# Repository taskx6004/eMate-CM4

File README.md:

# eMate-CM4
Yet another CM4 form-factor design for eMate laptop conversion kit.

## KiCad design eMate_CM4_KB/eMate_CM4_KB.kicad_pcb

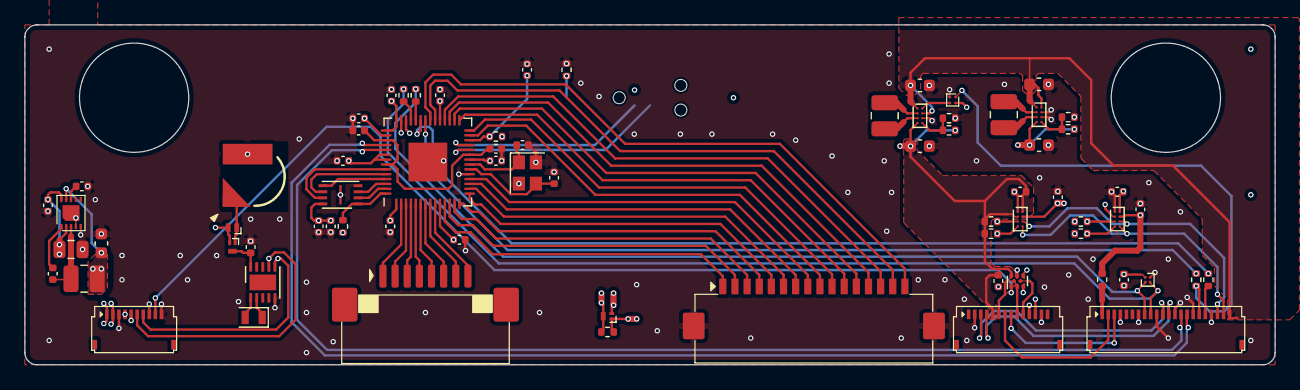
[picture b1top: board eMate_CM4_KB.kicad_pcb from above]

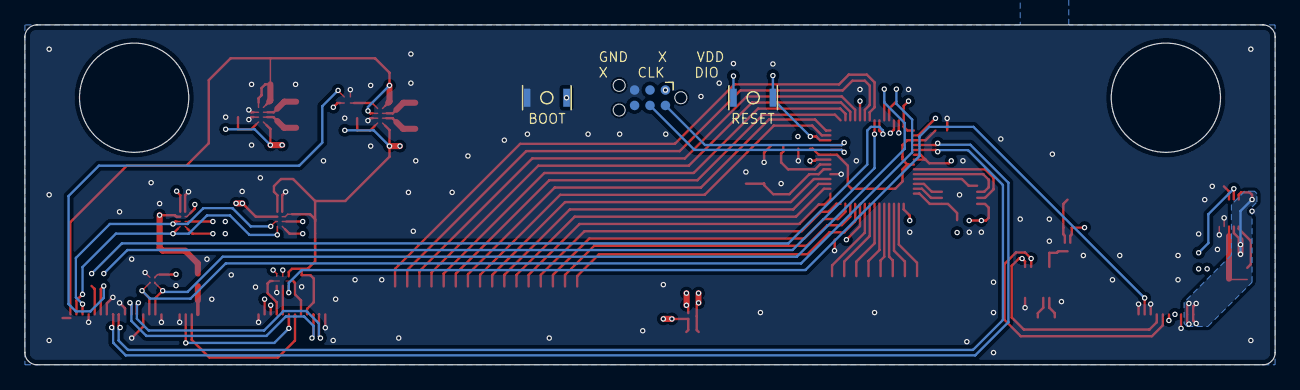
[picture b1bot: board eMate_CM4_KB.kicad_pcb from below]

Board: 4 copper layers, 103.0 x 28.0 mm, 75 parts (3 on the bottom side), 85 nets.

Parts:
BT1: XH414HG-IV01E
C1, C4, C6, C9, C13, C15, C17, C18, C19, C20, C21, C22, C23, C24, C27, C28, C29, C30: 100nF; C_0402_1005Metric
C2, C7, C10: 22uF; C_0603_1608Metric
C3, C11: 47uF; C_0603_1608Metric
C5: 4.7uF; C_0805_2012Metric
C8: 1uF; C_0402_1005Metric
C12, C14, C16: 2.2uF; C_0402_1005Metric
C25, C26: 15pF; C_0402_1005Metric
D1, D3: BAT54CM,315; Diodes_DFN1006-3
D2: BAS70L,315; Diodes_DFN1006-2
J1: FH34SRJ-22S-0.5SH(50)
J2: FH34SRJ-14S-0.5SH(50)
J3: FH34SRJ-10S-0.5SH(50)
J4: 522070833
J5: FH12-16S-1SH(55)
J6: TC2030-NL
L1, L3: 1uH; L_1008_2520Metric
L2: 10uH; L_1008_2520Metric
R1, R4, R6: 511k; R_0402_1005Metric
R2, R5: 91k; R_0402_1005Metric
R3, R17: 0; R_0402_1005Metric
R7, R8, R9, R10, R11, R12: 1k; R_0402_1005Metric
R13, R14, R15, R16: 4.7k; R_0402_1005Metric
SW1, SW2: EVPAWBD4A; EVPAWBA2A
U1: PCF85063ATL; DFN-10-1EP_2.6x2.6mm_P0.5mm_EP1.3x2.2mm
U2, U6: TPS631010YBGR; Texas_DSBGA-8_0.705x1.468mm_Layout2x4_P0.4mm
U3: SN74LVC1G06YZVR
U4: MAX77596ETBB+; MAX77596ETBB+T
U5: TCA9536ADTMR
U7: CAT24C32C5CTR; WLP-4_0.83x0.83mm_P0.4mm
U8: W25Q16JVUXIQ
U9: RP2040; QFN-56-1EP_7x7mm_P0.4mm_EP3.2x3.2mm
U10, U11: PCA9306YZTR; Texas_DSBGA-8_0.705x1.468mm_Layout2x4_P0.4mm
Y1: FC-12M32.768KHZ7PF20PPM; Crystal_SMD_2012-2Pin_2.0x1.2mm
Y2: 12MHz; Crystal_SMD_2520-4Pin_2.5x2.0mm

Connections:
3V3: C28.2, C30.2, R17.2, U10.B2 (VREF2), U11.B2 (VREF2)
3V3_BB1: C3.1, C9.2, C27.2, J2.5, J3.4, J3.5, R1.1, R13.2, R14.2, U2.D1 (VOUT), U5.7 (Vcc), U10.A2 (EN), U10.B1 (VREF1)
3V3_BB2: C12.2, C13.2, C16.2, C17.2, C18.2, C19.2, C20.2, C21.2, C22.2, C23.2, C29.2, D1.2, D2.2 (A), D3.3, J6.1 (VCC), R3.2, R6.1, R15.2, R16.2, U3.A2 (VDD), U7.A1 (VCC), U8.8 (VCC), U9.1 (IOVDD), U9.10 (IOVDD), U9.22 (IOVDD), U9.33 (IOVDD), U9.42 (IOVDD), U9.43 (ADC_AVDD), U9.44 (VREG_IN), U9.48 (USB_VDD), U9.49 (IOVDD), U11.A2 (EN), U11.B1 (VREF1)
/5V_~EN: J1.18, R10.2
/AD.DMICCLK: J1.2, J2.7
/AD.DMICIN: J1.3, J2.8
/CM4_I^{2}C_0.SCL: J1.20, U10.C2 (SCL2), U11.C2 (SCL2)
/CM4_I^{2}C_0.SDA: J1.21, U10.D2 (SDA2), U11.D2 (SDA2)
/CM4_I^{2}C_ID.SCL: J1.8, R11.2, U7.B1 (SCL)
/CM4_I^{2}C_ID.SDA: J1.9, R12.2, U7.B2 (SDA)
/EXT.D+: J1.11, J2.3
/EXT.D-: J1.12, J2.4
/FCM.ALS_SCL: J2.11, R13.1, U10.C1 (SCL1)
/FCM.ALS_SDA: J2.12, R14.1, U10.D1 (SDA1)
/FCM.ASL_INT: J2.10, U5.4 (P3/~INT)
/FCM.CAM_SW: J2.6, U5.8 (P1)
/FCM.MIC_SW: J2.9, U5.2
/HUB.D2+: J1.14, U9.47 (USB_DP)
/HUB.D2-: J1.15, U9.46 (USB_DM)
/I2C_GPIO.P0: J3.9, U5.1 (P0)
/M2.EN: J1.17, R9.2, U3.A1 (A)
/SCL: J3.6, R15.1, U1.7 (SCL), U5.5 (SCL), U9.41 (GPIO29_ADC3), U11.C1 (SCL1)
/SDA: J3.7, R16.1, U1.6 (SDA), U5.6 (SDA), U9.40 (GPIO28_ADC2), U11.D1 (SDA1)
GND: BT1.2 (-), C1.1, C2.2, C3.2, C5.2, C6.2, C7.2, C8.2, C9.1, C10.2, C11.2, C12.1, C13.1, C14.1, C15.1, C16.1, C17.1, C18.1, C19.1, C20.1, C21.1, C22.1, C23.1, C24.1, C25.1, C26.1, C27.1, C28.1, C29.1, C30.1, J1.4, J1.7, J1.10, J1.13, J1.16, J1.19, J2.2, J2.13, J3.3, J3.8, J3.10, J5.MP (MountPin), J6.5 (GND), R2.2, R5.2, R7.2, SW2.2, U1.5 (VSS), U2.C2 (GND), U3.B1 (GND), U4.4 (PGND), U4.5 (AGND), U4.EP (GND), U5.3 (GND), U6.B2 (MODE), U6.C2 (GND), U7.A2 (VSS), U8.4 (GND), U8.9 (EP), U9.19 (TESTEN), U9.57 (GND), U10.A1 (GND), U11.A1 (GND), Y2.2, Y2.4
HVSYS: C5.1, C6.1, J3.1, J3.2, U4.2 (SUP), U4.10 (EN)
unnamed: BT1.1 (+), D1.1, D2.1 (K)
unnamed: J1.1, R17.1
unnamed: J4.1, U9.2 (GPIO0)
unnamed: J4.2, U9.3 (GPIO1)
unnamed: J4.3, U9.4 (GPIO2)
unnamed: J4.4, U9.5 (GPIO3)
unnamed: J4.5, U9.6 (GPIO4)
unnamed: J4.6, U9.7 (GPIO5)
unnamed: J4.7, U9.8 (GPIO6)
unnamed: J4.8, U9.9 (GPIO7)
unnamed: J5.1, U9.11 (GPIO8)
unnamed: J5.2, U9.12 (GPIO9)
unnamed: J5.3, U9.13 (GPIO10)
unnamed: J5.4, U9.14 (GPIO11)
unnamed: J5.5, U9.15 (GPIO12)
unnamed: J5.6, U9.16 (GPIO13)
unnamed: J5.7, U9.17 (GPIO14)
unnamed: J5.8, U9.18 (GPIO15)
unnamed: J5.9, U9.27 (GPIO16)
unnamed: J5.10, U9.28 (GPIO17)
unnamed: J5.11, U9.29 (GPIO18)
unnamed: J5.12, U9.30 (GPIO19)
unnamed: J5.13, U9.31 (GPIO20)
unnamed: J5.14, U9.32 (GPIO21)
unnamed: J5.15, U9.34 (GPIO22)
unnamed: J5.16, U9.35 (GPIO23)
unnamed: J6.4 (SWCLK), U9.24 (SWCLK)
unnamed: J6.2 (SWDIO), U9.25 (SWD)
unnamed: R7.1, SW1.1
unnamed: R8.1, SW2.1
unnamed: U1.1 (OSCI), Y1.2
unnamed: U1.2 (OSCO), Y1.1
unnamed: C1.2, D1.3, U1.10 (VDD)
unnamed: U2.A2 (EN), U3.B2 (~Y)
unnamed: R1.2, R2.1, U2.D2 (FB)
unnamed: L1.1, U2.B1 (LX1)
unnamed: L1.2, U2.C1 (LX2)
unnamed: C8.1, U4.8 (BIAS)
unnamed: C4.1, U4.1 (BST)
unnamed: C4.2, L2.1, U4.3 (LX)
unnamed: C7.1, D3.2, L2.2, U4.9 (OUT/FB)
unnamed: R4.2, R5.1, U6.D2 (FB)
unnamed: L3.1, U6.B1 (LX1)
unnamed: L3.2, U6.C1 (LX2)
unnamed: C11.1, D3.1, R3.1, R4.1, U6.D1 (VOUT)
unnamed: U8.6 (CLK), U9.52 (QSPI_SCLK)
unnamed: U8.5 (DI(IO0)), U9.53 (QSPI_SD0)
unnamed: U8.2 (DO(IO1)), U9.55 (QSPI_SD1)
unnamed: U8.3 (IO2), U9.54 (QSPI_SD2)
unnamed: U8.7 (IO3), U9.51 (QSPI_SD3)
unnamed: R8.2, U8.1 (~CS), U9.56 (QSPI_SS)
unnamed: R9.1, U9.36 (GPIO24)
unnamed: R10.1, U9.37 (GPIO25)
unnamed: R11.1, U9.38 (GPIO26_ADC0)
unnamed: R12.1, U9.39 (GPIO27_ADC1)
unnamed: C24.2, R6.2, SW1.2, U9.26 (RUN)
unnamed: C14.2, C15.2, U9.23 (DVDD), U9.45 (VREG_VOUT), U9.50 (DVDD)
unnamed: C25.2, U9.20 (XIN), Y2.3
unnamed: C26.2, U9.21 (XOUT), Y2.1
VSYS: C2.1, C10.1, J1.22, U2.A1 (VIN), U2.B2 (MODE), U6.A1 (VIN), U6.A2 (EN)

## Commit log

2024-03-10 inital commit
    inital commit, designs are tested with actual PCBA
2024-03-18 add schematic in PDF form
